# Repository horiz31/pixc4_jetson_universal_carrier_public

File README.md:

# PixC4 Jetson Universal Carrier Board Design Template
Schematic and Kicad board design for a PixC4-Jetson Universal Carrier Board

This project is intended to help users design a custom carrier board for the PixC4-Jetson. It contains a verified working design providing wide-input DC power regulation and typical connector pinouts.

A STEP file with 3D models is available here: https://drive.google.com/file/d/1p-Tw4490VoOuMsqg2tXlwOgqGBfQfWUK/view?usp=sharing

Designed in KiCad 5.1.8. KiCad is available for free download: https://www.kicad.org/download/

## Design Notes
#### Power
Power regulation is handled by two TI TPS54561QDPRRQ1 dc-dc converters. One is used to power the +5V bus, which is used to power the Nvidia Jetson. The other is used to power the +5V_FMU bus which is used to power the FMU. In general it is good design practice to separate the power system between that used for the Jetson and the FMU as we have done in this design. This way, even if an issue causes the Jetson bus to go into over-current protection, the core FMU may remain functional.

It is possible to implement a Power Selection Unit (PSU) for the FMU, providing even further redundancy. The ~VDD_POWERA_VALID and ~VDD_POWERB_VALID lines can be used in conjunction with a PSU to inform the FMU about the active power source. Note that the FMU USB port on the PixC4-Jetson can also power the FMU system, as this is useful for setup and downloading log files.

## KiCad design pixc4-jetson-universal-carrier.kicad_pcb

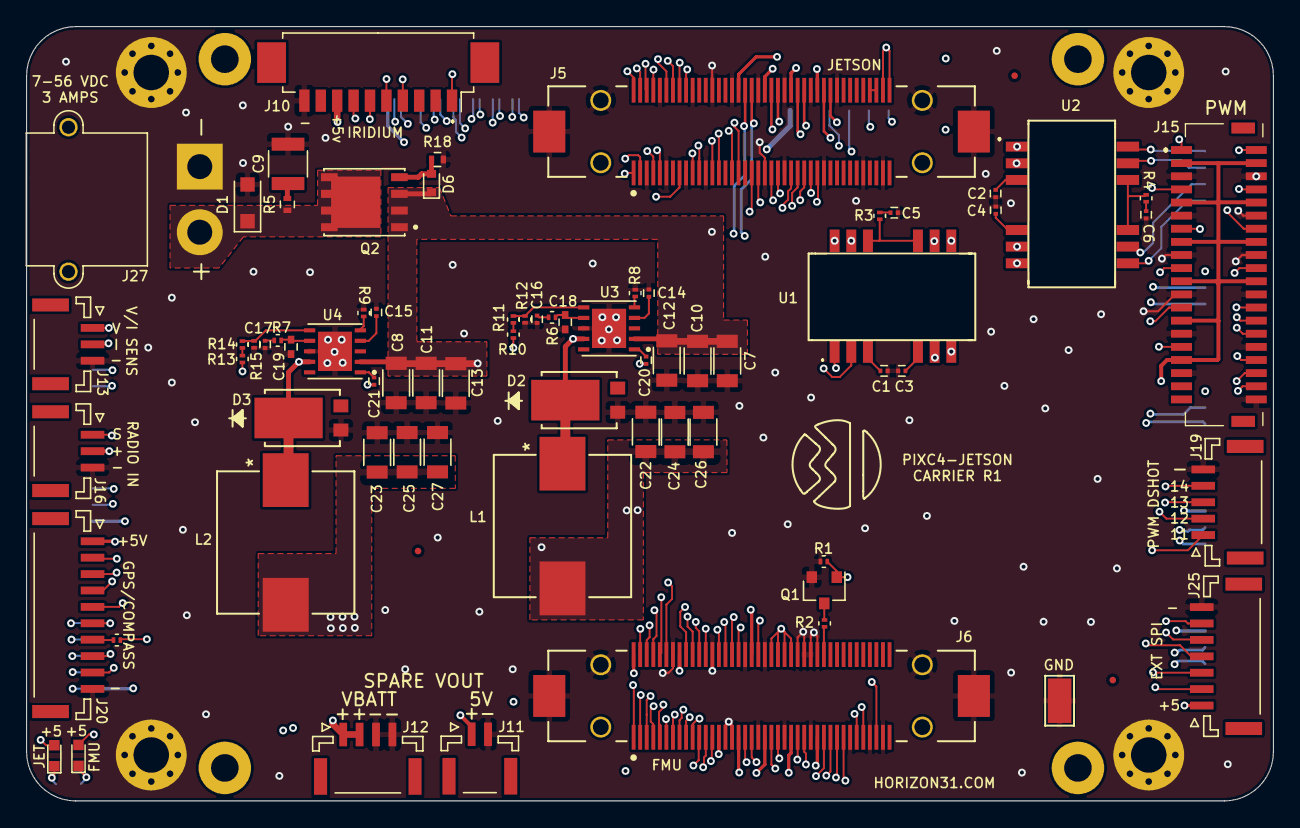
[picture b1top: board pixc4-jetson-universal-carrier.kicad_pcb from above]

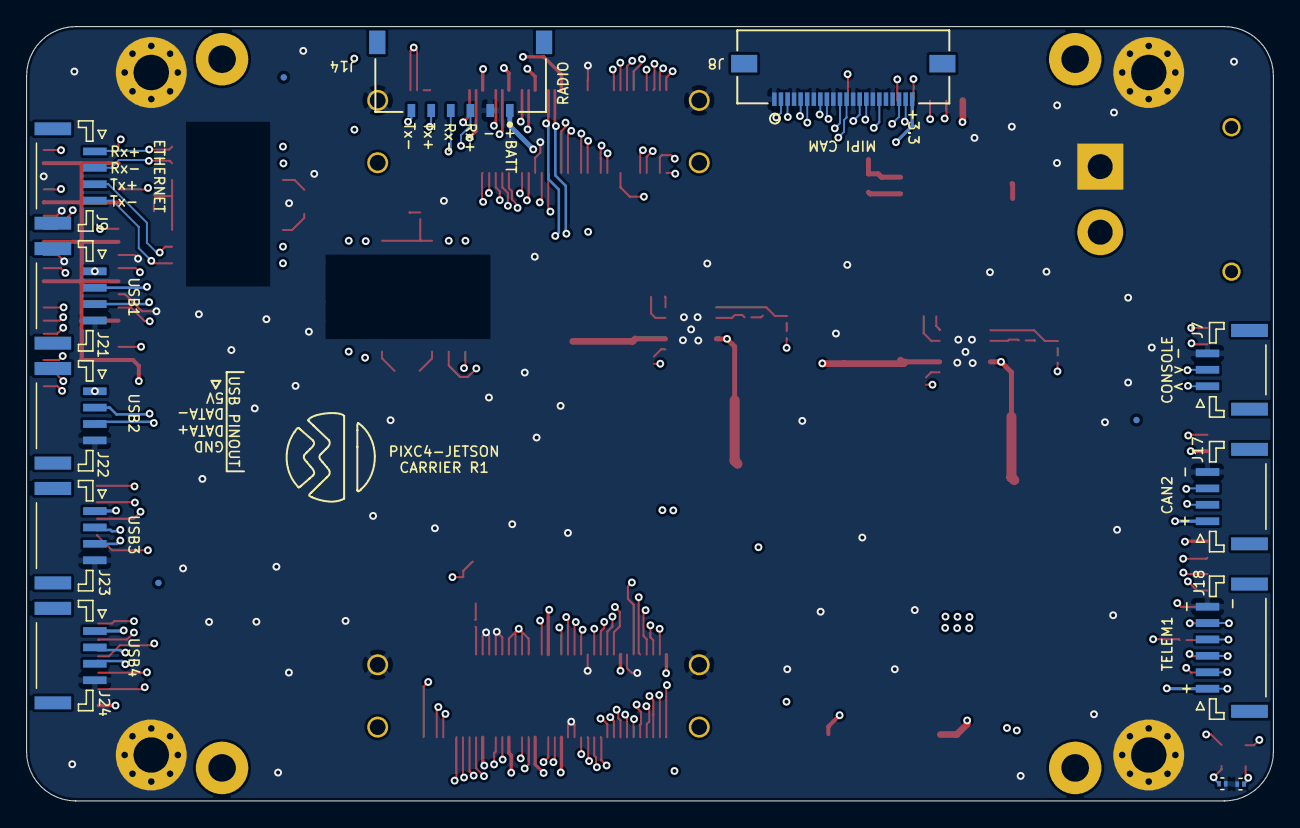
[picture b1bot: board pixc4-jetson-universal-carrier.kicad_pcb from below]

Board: 8 copper layers, 95.0 x 59.0 mm, 94 parts (15 on the bottom side), 129 nets.

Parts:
C1, C2, C3, C4, C20, C21: 0.1uF; C_0201
C5, C6: 1000pF; C_0201
C7, C8, C10, C11, C12, C13: 2.2uF 100V; C_1206
C9: 10uF 100V; C_1210
C14, C15: 10nF; C_0201
C16, C17: 4.7nF; C_0201
C18, C19: 47pF; C_0402
C22, C23, C24, C25, C26, C27: 47uF 10V; C_1206
D1: TVS; D_SOD-123F
D2, D3: PDS760-13
D4, D5: LED_G; LED_0603
D6: D_Zener; D_SOD-523
FID1, FID2, FID3, FID4, FID5, FID6: Fiducial; Fiducial_0.5mm_Dia_1mm_Outer
J1, J2, J3, J4: Conn_01x01; MountingHole_2.7mm_M2.5_Pad_Via
J5, J6: FX23L-80P-0.5SV10; Hirose-FX23L-80P-0.5SV8-MFG
J7, J13, J16: Conn_01x03; JST_GH_SM03B-GHS-TB_03x1.25mm_Angled
J8: Conn_01x22; 505110-2291
J9, J12, J17, J21, J22, J23, J24: Conn_01x04; JST_GH_SM04B-GHS-TB_04x1.25mm_Angled
J10: 0532617010; Molex_PicoBlade_53261-1071_10x1.25mm_Angled
J11: Conn_01x02; JST_GH_SM02B-GHS-TB_02x1.25mm_Angled
J14: 504050-0691; Molex-504050-0691-0-0-MFG
J15: 5015714007
J18: Conn_01x06; JST_GH_SM06B-GHS-TB_06x1.25mm_Angled
J19: Conn_01x05; JST_GH_SM05B-GHS-TB_05x1.25mm_Angled
J20: Conn_01x10; JST_GH_SM10B-GHS-TB_10x1.25mm_Angled
J25: Conn_01x07; JST_GH_SM07B-GHS-TB_07x1.25mm_Angled
J27: XT30PW-M; AMASS_XT30PW-M_1x02_P2.50mm_Horizontal
L1, L2: ASPIAIG-F1040-7R3M-T
Q1: Q_NMOS_GSD; SOT-23
Q2: FDWS9508L; TRANS_FDMS0300S
R1: 10K; R_0201
R2: 220; R_0201
R3, R4: 75; R_0201
R5: 750m; R_0402
R6, R7: 16.9K; R_0201
R8, R9: 243K; R_0201
R10, R13: 49.9; R_0201
R11, R14: 53.6K; R_0201
R12, R15: 10.2K; R_0201
R16, R17: 1.0K; R_0201
R18: 10K; R_0402
R19: 100; R_0201
TP1: TestPoint; Test_Point_Keystone_5015_Micro-Minature
U1, U2: HX0068ANLT; HX0068ANLT_r2
U3, U4: TPS54561QDPRRQ1; SON80P400X400X80-11N
U5: DoodleSmart; Doodle

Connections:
3V3_SYS: J5.79, J5.80, J8.22
+1V8: J5.77, J5.78
+5V: C23.1, C25.1, C27.1, D4.2, J5.81, J5.82, J6.81, J6.82, J10.8, J11.1, L2.2, R13.1
+5V_FMU: C22.1, C24.1, C26.1, D5.2, J6.62, J6.63, J6.64, J6.65, L1.2, Q1.1, R1.1, R10.1
+BATT: C7.1, C8.1, C10.1, C11.1, C12.1, C13.1, D6.1, J12.1, J12.2, J14.1, Q2.1, Q2.2, Q2.3, U3.2, U4.2
+VDD_5V_PERIPH: J6.17, J6.21, J6.25, J6.29, J6.41, J6.48, J15.26, J15.34, J17.1, J18.1, J20.1, J25.1
+VDD_5V_RADIO: J6.59, J16.2
+VDD_SERVO: J6.38, J15.3, J15.4, J15.9, J15.10, J15.15, J15.16, J15.21, J15.22, J15.27, J15.33
BATT_CURRENT_SENS_PROT: J6.35, J13.2
BATT_VOLTAGE_SENS_PROT: J6.36, J13.1
BUZZER_OUT: J6.57, J20.9
CAM1_C_N: J5.14, J8.8
CAM1_C_P: J5.13, J8.9
CAM1_D0_N: J5.17, J8.2
CAM1_D0_P: J5.16, J8.3
CAM1_D1_N: J5.11, J8.5
CAM1_D1_P: J5.10, J8.6
CAM1_D2_N: J5.23, J8.11
CAM1_D2_P: J5.22, J8.12
CAM1_D3_N: J5.20, J8.14
CAM1_D3_P: J5.19, J8.15
CAM_GPIO: J5.8, J8.17
CAM_SCL0: J5.5, J8.20
CAM_SDA0: J5.4, J8.21
CAN_H_1+: J6.26, J15.28
CAN_H_2+: J6.22, J17.2
CAN_L_1-: J6.27, J15.30
CAN_L_2-: J6.23, J17.3
ETH_RADIO_RX_N: J5.47, U1.2
ETH_RADIO_RX_P: J5.46, U1.1
ETH_RADIO_RX_POSTMAG_N: J14.4, U1.11
ETH_RADIO_RX_POSTMAG_P: J14.3, U1.12
ETH_RADIO_TX_N: J5.49, U1.6
ETH_RADIO_TX_P: J5.48, U1.5
ETH_RADIO_TX_POSTMAG_N: J14.6, U1.7
ETH_RADIO_TX_POSTMAG_P: J14.5, U1.8
ETH_SPARE_RX_N: J5.43, U2.2
ETH_SPARE_RX_P: J5.44, U2.1
ETH_SPARE_RX_POSTMAG_N: J9.2, U2.11
ETH_SPARE_RX_POSTMAG_P: J9.1, U2.12
ETH_SPARE_TX_N: J5.41, U2.6
ETH_SPARE_TX_P: J5.42, U2.5
ETH_SPARE_TX_POSTMAG_N: J9.4, U2.7
ETH_SPARE_TX_POSTMAG_P: J9.3, U2.8
FMU-CH1-PROT: J6.9, J15.14
FMU-CH2-PROT: J6.10, J15.20
FMU-CH3-PROT: J6.11, J19.1
FMU-CH4-PROT: J6.12, J19.2
FMU-CH5-PROT: J6.13, J19.3
FMU-CH6-PROT: J6.14, J19.4
FMU_I2C_1_SCL: J6.51, J20.4
FMU_I2C_1_SDA: J6.52, J20.5
FMU_I2C_2_SCL: J6.18, J15.36
FMU_I2C_2_SDA: J6.19, J15.38
GND: C1.2, C2.2, C3.2, C4.2, C5.2, C6.2, C7.2, C8.2, C9.2, C10.2, C11.2, C12.2, C13.2, C14.2, C15.2, C16.2, C17.2, C18.2, C19.2, C22.2, C23.2, C24.2, C25.2, C26.2, C27.2, D1.2, D2.2, D3.2, J1.1, J2.1, J3.1, J4.1, J5.3, J5.6, J5.9, J5.12, J5.18, J5.21, J5.24, J5.30, J5.36, J5.39, J5.45, J5.50, J5.53, J5.56, J5.60, J5.64, J5.68, J5.72, J5.83, J5.84, J5.85, J5.86, J6.15, J6.16, J6.20, J6.24, J6.28, J6.34, J6.37, J6.39, J6.47, J6.53, J6.58, J6.61, J6.66, J6.67, J6.68, J6.69, J6.83, J6.84, J6.85, J6.86, J7.3, J8.1, J8.4, J8.7, J8.10, J8.13, J8.16, J8.19, J10.10, J11.2, J12.3, J12.4, J13.3, J14.2, J15.5, J15.6, J15.11, J15.12, J15.17, J15.18, J15.23, J15.24, J15.29, J15.32, J15.35, J15.40, J16.3, J17.4, J18.6, J19.5, J20.10, J21.4, J22.4, J23.4, J24.4, J25.7, J27.1, Q1.2, R1.2, R8.1, R9.1, R12.2, R15.2, R16.2, R17.2, R18.2, TP1.1, U3.8, U3.11, U4.8, U4.11
GPS1_RX: J6.50, J20.3
GPS1_TX: J6.49, J20.2
IO-CH1-PROT: J6.1, J15.1
IO-CH2-PROT: J6.2, J15.7
IO-CH3-PROT: J6.3, J15.13
IO-CH4-PROT: J6.4, J15.19
IO-CH5-PROT: J6.5, J15.25
IO-CH6-PROT: J6.6, J15.31
IO-CH7-PROT: J6.7, J15.2
IO-CH8-PROT: J6.8, J15.8
IRID_NA_3.3: J5.26, J10.4
IRID_ON_OFF_3.3: J5.29, J10.7
IRID_RING_3.3: J5.27, J10.5
IRID_RX_OUT_3.3: J5.25, J10.1
IRID_TX_IN_3.3: J5.28, J10.6
unnamed: C1.1, U1.3
unnamed: C2.1, U2.3
unnamed: C3.1, U1.4
unnamed: C4.1, U2.4
unnamed: C5.1, R3.1
unnamed: C6.1, R4.1
unnamed: C9.1, R5.2
unnamed: C14.1, U3.4
unnamed: C15.1, U4.4
unnamed: C16.1, R6.1
unnamed: C17.1, R7.1
unnamed: C18.1, R6.2, U3.7
unnamed: C19.1, R7.2, U4.7
unnamed: C20.1, D2.1, L1.1, U3.9
unnamed: C20.2, U3.1
unnamed: C21.1, D3.1, L2.1, U4.9
unnamed: C21.2, U4.1
unnamed: D1.1, J27.2, Q2.5, Q2.6, Q2.7, Q2.8, Q2.9, R5.1
unnamed: D4.1, R16.1
unnamed: D5.1, R17.1
unnamed: D6.2, Q2.4, R18.1
unnamed: J20.7, R19.1
unnamed: Q1.3, R2.2
unnamed: R3.2, U1.9, U1.10
unnamed: R4.2, U2.9, U2.10
unnamed: R8.2, U3.5
unnamed: R9.2, U4.5
unnamed: R10.2, R11.1
unnamed: R11.2, R12.1, U3.6
unnamed: R13.2, R14.1
unnamed: R14.2, R15.1, U4.6
PORT_VBUS_2: J5.69, J21.1
PORT_VBUS_3: J5.65, J22.1
PORT_VBUS_4: J5.61, J23.1
PORT_VBUS_5: J5.57, J24.1
RC_INPUT: J6.60, J16.1
SAFETY_SWITCH_IN: J6.54, J20.6
SAFETY_VDD: J6.56, J20.8
SPI5_CS1_EXTERNAL1: J6.45, J25.5
SPI5_CS2_EXTERNAL1: J6.46, J25.6
SPI5_MISO_EXTERNAL1: J6.43, J25.3
SPI5_MOSI_EXTERNAL1: J6.44, J25.4
SPI5_SCK_EXTERNAL1: J6.42, J25.2
TELEM1_CTS: J6.31, J18.4
TELEM1_RTS: J6.30, J18.5
TELEM1_RX: J6.32, J18.3
TELEM1_TX: J6.33, J18.2
USB2+: J5.70, J21.3
USB2-: J5.71, J21.2
USB3+: J5.66, J22.3
USB3-: J5.67, J22.2
USB4+: J5.62, J23.3
USB4-: J5.63, J23.2
USB5+: J5.58, J24.3
USB5-: J5.59, J24.2
XAVIER_CONSOLE_RX_IN: J5.1, J7.1
XAVIER_CONSOLE_TX_OUT: J5.2, J7.2
~SAFETY_SWITCH_LED_OUT: J6.55, R19.2
~VDD_POWERA_VALID: J6.70, R2.1

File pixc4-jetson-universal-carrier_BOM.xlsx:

PixC4-Jetson Universal Carrier Rev 1
Item | Qty | Reference(s) | Value | LibPart | Footprint | Part Num | Notes
1 | 6 | C1, C2, C3, C4, C20, C21 | 0.1uF | Device:C | Capacitors_SMD:C_0201 | GRM033R61E104KE14J
2 | 2 | C5, C6 | 1000pF | Device:C | Capacitors_SMD:C_0201 | GRM033R71H102KA12D
3 | 6 | C7, C8, C10, C11, C12, C13 | 2.2uF 100V | Device:C | Capacitors_SMD:C_1206 | 12061C225KAT2A
4 | 1 | C9 | 10uF 100V | Device:C | Capacitors_SMD:C_1210 | GRM32EC72A106KE05L
5 | 2 | C14, C15 | 10nF | Device:C | Capacitors_SMD:C_0201 | GRM033R71E103KE14D
6 | 2 | C16, C17 | 4.7nF | Device:C | Capacitors_SMD:C_0201 | GRM033R61E472KA12D
7 | 2 | C18, C19 | 47pF | Device:C | Capacitors_SMD:C_0402 | C0402C470J3RACAUTO
8 | 6 | C22, C23, C24, C25, C26, C27 | 47uF 10V | Device:C | Capacitors_SMD:C_1206 | CL31A476MPHNNNE
9 | 1 | D1 | TVS | osrf_device_fork:TVS | Diodes_SMD:D_SOD-123F | ATV02W101B-HF
10 | 2 | D2, D3 | PDS760-13 | Device:D_Schottky | UVDL:PDS760-13 | PDS760-13
11 | 2 | D4, D5 | LED_G | Device:LED | LEDs:LED_0603 | 150060VS75000
12 | 1 | D6 | D_Zener | Device:D_Zener | Diodes_SMD:D_SOD-523 | MM5Z12VT1G
13 | 6 | FID1, FID2, FID3, FID4, FID5, FID6 | Fiducial | Mechanical:Fiducial | Fiducials:Fiducial_0.5mm_Dia_1mm_Outer | DNI | DNI
14 | 4 | J1, J2, J3, J4 | Conn_01x01 | Connector_Generic:Conn_01x01 | Mounting_Holes:MountingHole_2.7mm_M2.5_Pad_Via | DNI | DNI
15 | 2 | J5, J6 | FX23L-80P-0.5SV10 | fx23l-80p-0.5sv8:FX23L-80P-0.5SV8 | UVDL:Hirose-FX23L-80P-0.5SV8-MFG | FX23L-80P-0.5SV10
16 | 3 | J7, J13, J16 | Conn_01x03 | Connector_Generic:Conn_01x03 | Connectors_JST:JST_GH_SM03B-GHS-TB_03x1.25mm_Angled | SM03B-GHS-TB(LF)(SN)
17 | 1 | J8 | Conn_01x22 | Connector_Generic:Conn_01x22 | UVDL:505110-2291 | 505110-2291
18 | 7 | J9, J12, J17, J21, J22, J23, J24 | Conn_01x04 | Connector_Generic:Conn_01x04 | Connectors_JST:JST_GH_SM04B-GHS-TB_04x1.25mm_Angled | SM04B-GHS-TB(LF)(SN)
19 | 1 | J10 | 532617010 | Connector_Generic:Conn_01x10 | Connectors_Molex:Molex_PicoBlade_53261-1071_10x1.25mm_Angled | 532617010
20 | 1 | J11 | Conn_01x02 | Connector_Generic:Conn_01x02 | Connectors_JST:JST_GH_SM02B-GHS-TB_02x1.25mm_Angled | SM02B-GHS-TB(LF)(SN)
21 | 1 | J14 | 504050-0691 | Connector_Generic:Conn_01x06 | UVDL:Molex-504050-0691-0-0-MFG | 504050-0691
22 | 1 | J15 | 5015714007 | Connector_Generic:Conn_02x20_Odd_Even | UVDL:5015714007 | 5015714007
23 | 1 | J18 | Conn_01x06 | Connector_Generic:Conn_01x06 | Connectors_JST:JST_GH_SM06B-GHS-TB_06x1.25mm_Angled | SM06B-GHS-TB(LF)(SN)
24 | 1 | J19 | Conn_01x05 | Connector_Generic:Conn_01x05 | Connectors_JST:JST_GH_SM05B-GHS-TB_05x1.25mm_Angled | SM05B-GHS-TB(LF)(SN)
25 | 1 | J20 | Conn_01x10 | Connector_Generic:Conn_01x10 | Connectors_JST:JST_GH_SM10B-GHS-TB_10x1.25mm_Angled | SM10B-GHS-TB(LF)(SN)
26 | 1 | J25 | Conn_01x07 | Connector_Generic:Conn_01x07 | Connectors_JST:JST_GH_SM07B-GHS-TB_07x1.25mm_Angled | SM07B-GHS-TB(LF)(SN)
27 | 1 | J27 | XT30PW-M | Connector_Generic:Conn_01x02 | UVDL:AMASS_XT30PW-M_1x02_P2.50mm_Horizontal | XT30PW-M
28 | 2 | L1, L2 | ASPIAIG-F1040-7R3M-T | Device:L | UVDL:ASPIAIG-F1040-7R3M-T | ASPIAIG-F1040-7R3M-T
29 | 1 | Q1 | Q_NMOS_GSD | Device:Q_NMOS_GSD | TO_SOT_Packages_SMD:SOT-23 | BSS214NH6327XTSA1
30 | 1 | Q2 | FDWS9508L | archangel:FDWS9508L | patrios:TRANS_FDMS0300S | FDWS9508L-F085
31 | 1 | R1 | 10K | Device:R | Resistors_SMD:R_0201 | ERJ-1GNF1002C
32 | 1 | R2 | 220 | Device:R | Resistors_SMD:R_0201 | ERJ-1GNF2200C
33 | 2 | R3, R4 | 75 | Device:R | Resistors_SMD:R_0201 | ERJ-1GNF75R0C
34 | 1 | R5 | 750m | Device:R | Resistors_SMD:R_0402 | ERJ-2BQJR75X
35 | 2 | R6, R7 | 16.9K | Device:R | Resistors_SMD:R_0201 | ERJ-1GNF1692C
36 | 2 | R8, R9 | 243K | Device:R | Resistors_SMD:R_0201 | ERJ-1GNF2433C
37 | 2 | R10, R13 | 49.9 | Device:R | Resistors_SMD:R_0201 | ERJ-1GEF49R9C
38 | 2 | R11, R14 | 53.6K | Device:R | Resistors_SMD:R_0201 | ERJ-1GNF5362C
39 | 2 | R12, R15 | 10.2K | Device:R | Resistors_SMD:R_0201 | ERJ-1GNF1022C
40 | 2 | R16, R17 | 1.0K | Device:R | Resistors_SMD:R_0201 | ERJ-1GEF1001C
41 | 1 | R18 | 10K | Device:R | Resistors_SMD:R_0402 | ERJ-PA2J103X
42 | 1 | R19 | 100 | Device:R | Resistors_SMD:R_0201 | ERJ-U01F1000C
43 | 2 | U1, U2 | HX0068ANLT | Microhard:HX0068ANLT | Nightcrawler:HX0068ANLT_r2 | HX0068ANLT
44 | 2 | U3, U4 | TPS54561QDPRRQ1 | TPS54561DPRR:TPS54561DPRR | UVDL:SON80P400X400X80-11N | TPS54561QDPRRQ1
45 | 1 | U5 | DoodleSmart | archangel:DoodleSmart | Nightcrawler:Doodle | DNI

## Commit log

2021-06-12 initial
